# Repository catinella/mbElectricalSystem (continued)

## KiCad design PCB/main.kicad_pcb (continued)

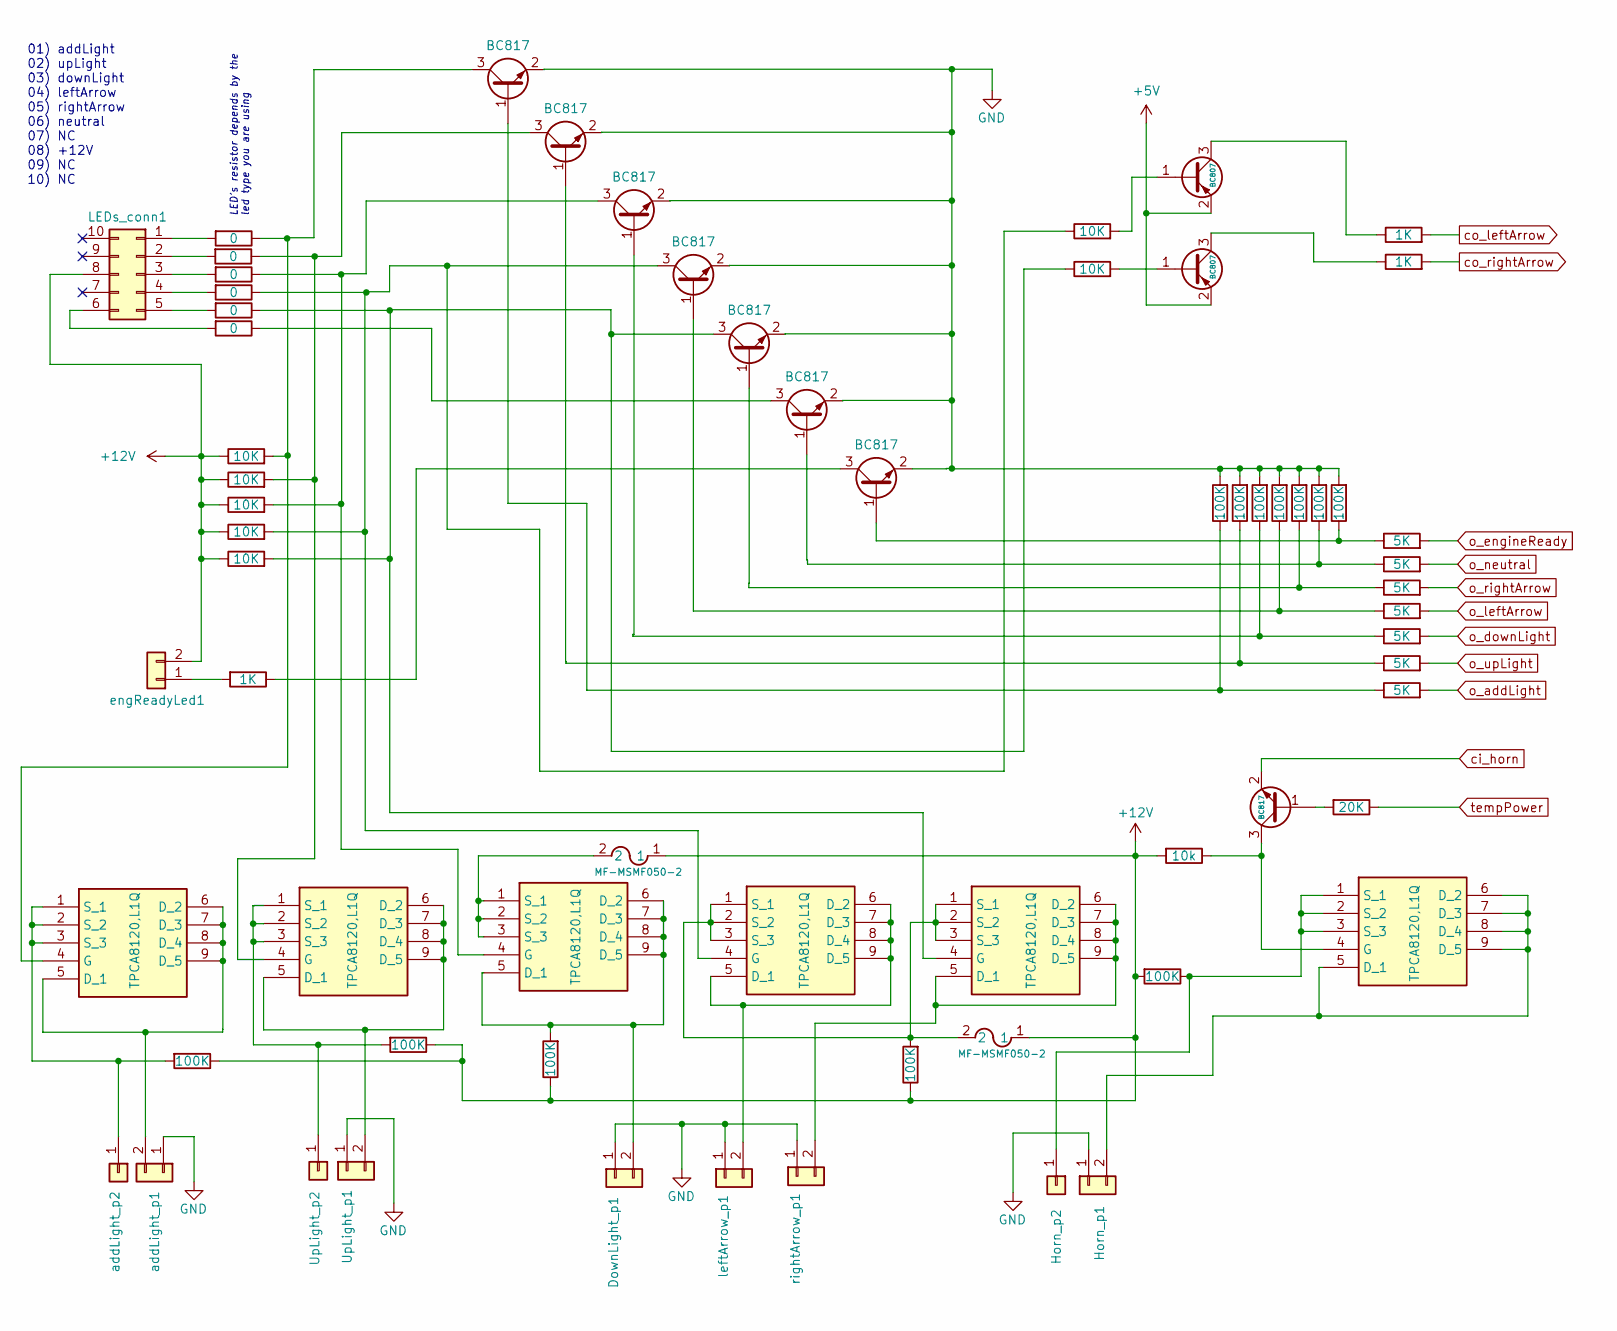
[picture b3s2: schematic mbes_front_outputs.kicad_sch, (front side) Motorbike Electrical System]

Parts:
DownLight_p1: Conn_01x02; PinHeader_1x02_P2.54mm_Vertical
F1, F2: MF-MSMF050-2; FUSE_F050-2
Horn_p1: Conn_01x02; JST_VH_B2P-VH-FB-B_1x02_P3.96mm_Vertical
Horn_p2: Conn_01x01; SolderWire-1sqmm_1x01_D1.4mm_OD2.7mm
LEDs_conn1: Conn_02x05_Counter_Clockwise; PinHeader_2x05_P2.54mm_Vertical
Q1, Q20: BC807; SOT-23
Q5, Q6, Q7, Q12, Q16, Q18: TPCA8120,L1Q; TPH4R003NLL1Q; Mouser Part Number 757-TPCA8120L1Q
Q8, Q9, Q10, Q11, Q13, Q14, Q15, Q17: BC817; SOT-23
RA3, RA4, RA5, RA6, RA7, RA8: 0; R_1206_3216Metric
RA9, RA10, RA11, RA12, RA13, RA37, RA38: 10K; R_1206_3216Metric
RA14, RA43, RA44: 1K; R_1206_3216Metric
RA15, RA16, RA17, RA18, RA19, RA20, RA22, RA23, RA24, RA25, RA27, RA28: 100K; R_1206_3216Metric
RA21: 10k; R_1206_3216Metric
RA29: 20K; R_1206_3216Metric
RA30, RA31, RA32, RA33, RA34, RA35, RA36: 5K; R_1206_3216Metric
UpLight_p1: Conn_01x02; JST_VH_B2P-VH-FB-B_1x02_P3.96mm_Vertical
UpLight_p2: Conn_01x01; SolderWire-1sqmm_1x01_D1.4mm_OD2.7mm
addLight_p1: Conn_01x02; JST_VH_B2P-VH-FB-B_1x02_P3.96mm_Vertical
addLight_p2: Conn_01x01; SolderWire-1sqmm_1x01_D1.4mm_OD2.7mm
engReadyLed1: Conn_01x02; PinHeader_1x02_P2.54mm_Vertical
leftArrow_p1: Conn_01x02; PinHeader_1x02_P2.54mm_Vertical
rightArrow_p1: Conn_01x02; PinHeader_1x02_P2.54mm_Vertical

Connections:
5V: Q1.2 (E), Q20.2 (E); also elsewhere on the board
+12V: F1.1, F2.1, LEDs_conn1.8, RA9.1, RA10.1, RA11.1, RA12.1, RA13.1, RA15.1, RA16.1, RA17.1, RA18.1, RA19.2, RA21.2, engReadyLed1.2; also elsewhere on the board
GND: DownLight_p1.1, Horn_p1.1, Q8.2 (E), Q9.2 (E), Q10.2 (E), Q11.2 (E), Q13.2 (E), Q14.2 (E), Q15.2 (E), RA20.2, RA22.2, RA23.2, RA24.2, RA25.2, RA27.2, RA28.2, UpLight_p1.1, addLight_p1.1, leftArrow_p1.1, rightArrow_p1.1; also elsewhere on the board
unnamed: DownLight_p1.2, Q7.5 (D_1), Q7.6 (D_2), Q7.7 (D_3), Q7.8 (D_4), Q7.9 (D_5), RA17.2
unnamed: Horn_p1.2, Q18.5 (D_1), Q18.6 (D_2), Q18.7 (D_3), Q18.8 (D_4), Q18.9 (D_5)
unnamed: Horn_p2.1, Q18.1 (S_1), Q18.2 (S_2), Q18.3 (S_3), RA19.1
unnamed: LEDs_conn1.1, RA4.2
unnamed: LEDs_conn1.2, RA3.2
unnamed: LEDs_conn1.3, RA5.2
unnamed: LEDs_conn1.4, RA6.2
unnamed: LEDs_conn1.5, RA7.2
unnamed: LEDs_conn1.6, RA8.2
unnamed: Q1.1 (B), RA37.2
unnamed: Q1.3 (C), RA43.1
unnamed: Q5.5 (D_1), Q5.6 (D_2), Q5.7 (D_3), Q5.8 (D_4), Q5.9 (D_5), addLight_p1.2
unnamed: Q5.4 (G), Q8.3 (C), RA4.1, RA9.2
unnamed: Q5.1 (S_1), Q5.2 (S_2), Q5.3 (S_3), RA15.2, addLight_p2.1
unnamed: Q6.5 (D_1), Q6.6 (D_2), Q6.7 (D_3), Q6.8 (D_4), Q6.9 (D_5), UpLight_p1.2
unnamed: Q6.4 (G), Q9.3 (C), RA3.1, RA10.2
unnamed: Q6.1 (S_1), Q6.2 (S_2), Q6.3 (S_3), RA16.2, UpLight_p2.1
unnamed: F2.2, Q7.1 (S_1), Q7.2 (S_2), Q7.3 (S_3)
unnamed: Q8.1 (B), RA20.1, RA36.1
unnamed: Q9.1 (B), RA22.1, RA35.1
unnamed: Q10.1 (B), RA23.1, RA34.1
unnamed: Q7.4 (G), Q10.3 (C), RA5.1, RA11.2
unnamed: Q11.1 (B), RA24.1, RA33.1
unnamed: Q11.3 (C), Q12.4 (G), RA6.1, RA12.2, RA37.1
unnamed: Q12.5 (D_1), Q12.6 (D_2), Q12.7 (D_3), Q12.8 (D_4), Q12.9 (D_5), leftArrow_p1.2
unnamed: F1.2, Q12.1 (S_1), Q12.2 (S_2), Q12.3 (S_3), Q16.1 (S_1), Q16.2 (S_2), Q16.3 (S_3), RA18.2
unnamed: Q13.1 (B), RA25.1, RA32.1
unnamed: Q13.3 (C), Q16.4 (G), RA7.1, RA13.2, RA38.1
unnamed: Q14.1 (B), RA27.1, RA31.1
unnamed: Q14.3 (C), RA8.1
unnamed: Q15.1 (B), RA28.1, RA30.1
unnamed: Q15.3 (C), RA14.1
unnamed: Q16.5 (D_1), Q16.6 (D_2), Q16.7 (D_3), Q16.8 (D_4), Q16.9 (D_5), rightArrow_p1.2
unnamed: Q17.1 (B), RA29.2
unnamed: Q17.3 (C), Q18.4 (G), RA21.1
unnamed: Q20.1 (B), RA38.2
unnamed: Q20.3 (C), RA44.1
unnamed: RA14.2, engReadyLed1.1
ci_horn: Q17.2 (E); also elsewhere on the board
co_leftArrow: RA43.2; also elsewhere on the board
co_rightArrow: RA44.2; also elsewhere on the board
o_addLight: RA36.2; also elsewhere on the board
o_downLight: RA34.2; also elsewhere on the board
o_engineReady: RA30.2; also elsewhere on the board
o_leftArrow: RA33.2; also elsewhere on the board
o_neutral: RA31.2; also elsewhere on the board
o_rightArrow: RA32.2; also elsewhere on the board
o_upLight: RA35.2; also elsewhere on the board
tempPower: RA29.1; also elsewhere on the board

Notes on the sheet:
LED's resistor depends by the led type you are using
01) addLight 02) upLight 03) downLight 04) leftArrow 05) rightArrow 06) neutral 07) NC 08) +12V 09) NC 10) NC

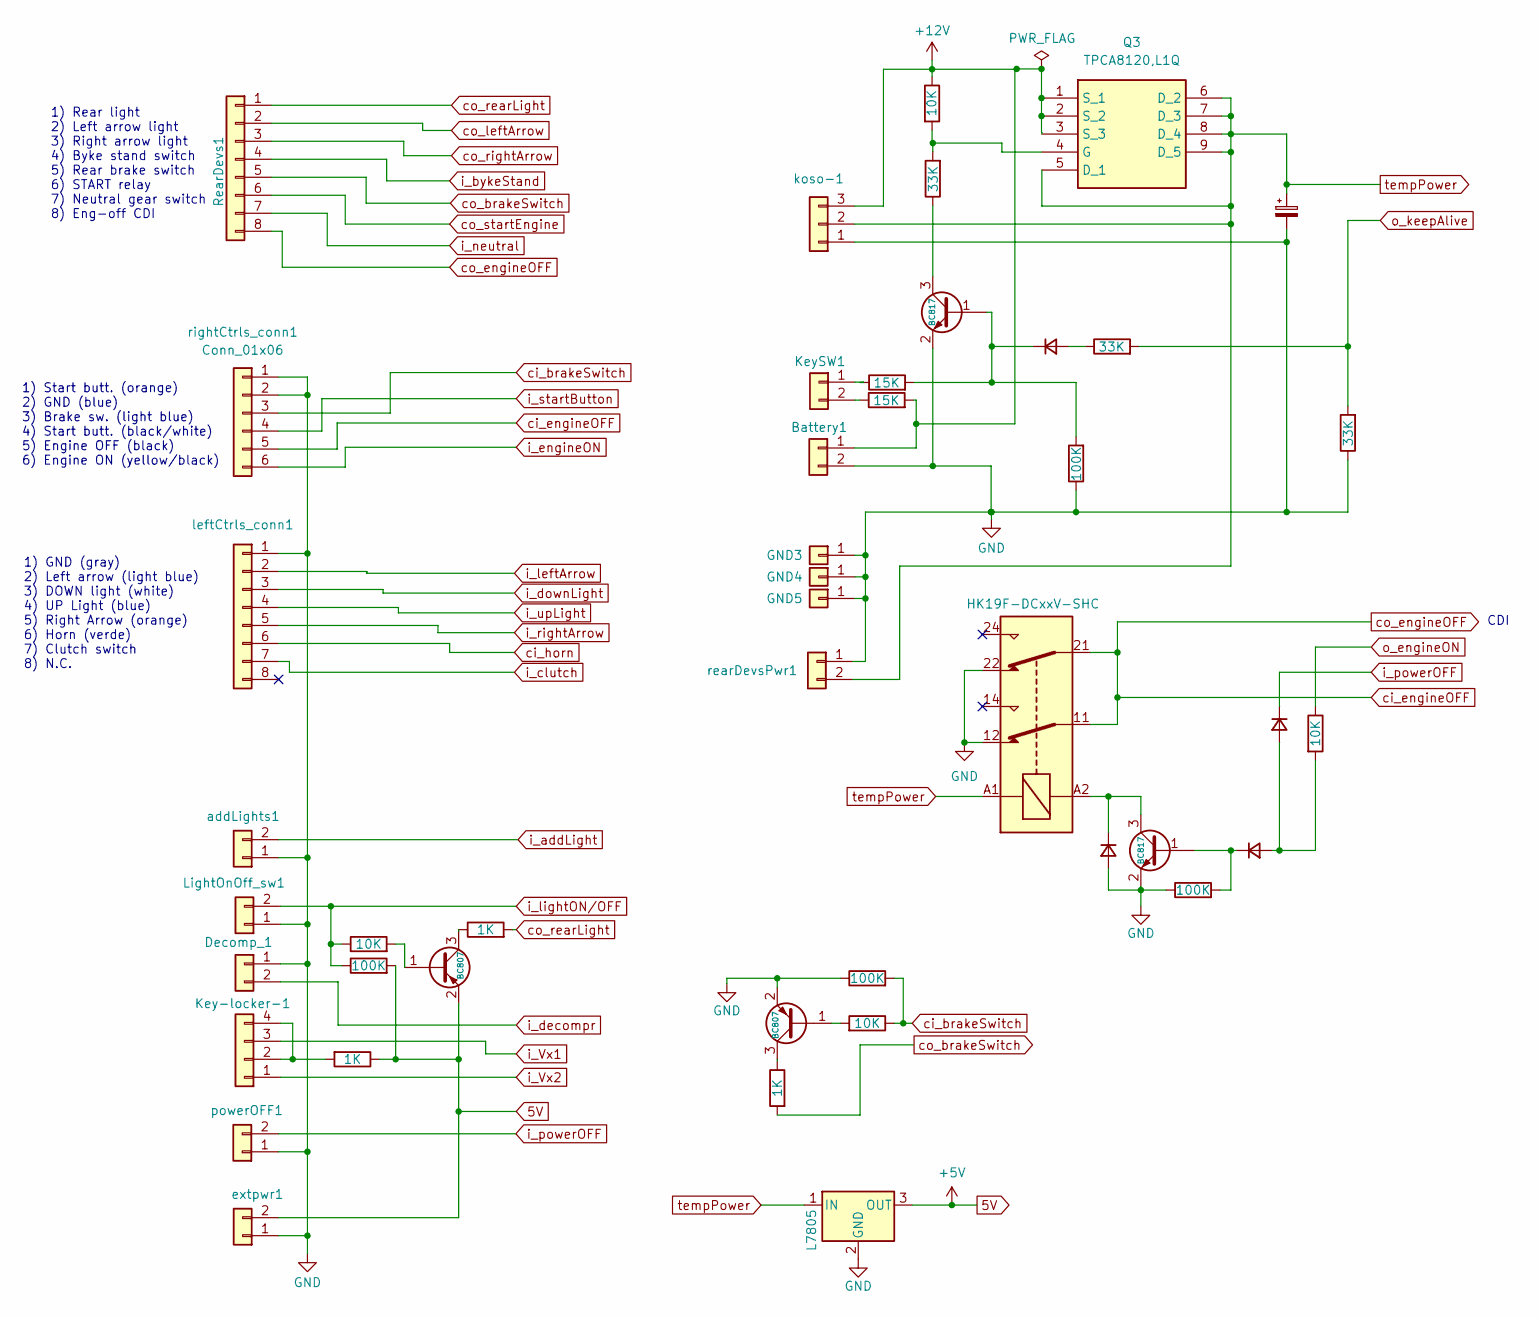
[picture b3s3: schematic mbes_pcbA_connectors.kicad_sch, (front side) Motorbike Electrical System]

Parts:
Battery1: Conn_01x02; JST_VH_B2P-VH-FB-B_1x02_P3.96mm_Vertical
C2: C_Polarized_Small; CP_Radial_D8.0mm_P2.50mm
D1, D2, D3: PMEG40T30ER; Nexperia_CFP3_SOD-123W
Decomp_1: Conn_01x02; PinHeader_1x02_P2.54mm_Vertical
GND3, GND4, GND5: Conn_01x01; SolderWire-1sqmm_1x01_D1.4mm_OD2.7mm
K1: HK19F-DCxxV-SHC; Relay_DPDT_Finder_30.22
Key-locker-1: Conn_01x04; PinHeader_1x04_P2.54mm_Vertical
KeySW1: Conn_01x02; PinHeader_1x02_P2.54mm_Vertical
LightOnOff_sw1: Conn_01x02; PinHeader_1x02_P2.54mm_Vertical
Q2, Q4: BC817; SOT-23
Q3: TPCA8120,L1Q; TPH4R003NLL1Q; Manufacturer_Part_Number TPCA8120,L1Q; Mouser Part Number 757-TPCA8120L1Q
Q22, Q24: BC807; SOT-23
R6: 1K; R_1206_3216Metric
R7, R8: 15K; R_1206_3216Metric
R9: 10K; R_1206_3216Metric
R10, R11, R12: 33K; R_1206_3216Metric
R13: 100K; R_1206_3216Metric
RA1, RA41, RA47: 100K; R_1206_3216Metric
RA2, RA40, RA46: 10K; R_1206_3216Metric
RA42, RA48: 1K; R_1206_3216Metric
RearDevs1: Conn_01x08; PinHeader_1x08_P2.54mm_Vertical
U2: L7805; TO-220-3_Vertical
addLights1: Conn_01x02; PinHeader_1x02_P2.54mm_Vertical
extpwr1: Conn_01x02; PinHeader_1x02_P2.54mm_Vertical
flyback-1: PMEG40T30ER; Nexperia_CFP3_SOD-123W
koso-1: Conn_01x03; PinHeader_1x03_P2.54mm_Vertical
leftCtrls_conn1: Conn_01x08; PinHeader_1x08_P2.54mm_Vertical
powerOFF1: Conn_01x02; PinHeader_1x02_P2.54mm_Vertical
rearDevsPwr1: Conn_01x02; PinHeader_1x02_P2.54mm_Vertical
rightCtrls_conn1: Conn_01x06; PinHeader_1x06_P2.54mm_Vertical

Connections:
5V: Q22.2 (E), R6.1, RA47.2, U2.3 (OUT), extpwr1.2; also elsewhere on the board
+12V: Battery1.1, Q3.1 (S_1), Q3.2 (S_2), Q3.3 (S_3), R7.2, R9.1, koso-1.3; also elsewhere on the board
GND: Battery1.2, C2.2, Decomp_1.1, GND3.1, GND4.1, GND5.1, K1.12, K1.22, LightOnOff_sw1.1, Q2.2 (E), Q4.2 (E), Q24.2 (E), R12.1, R13.1, RA1.1, RA41.1, U2.2 (GND), addLights1.1, extpwr1.1, flyback-1.2 (A), koso-1.1, leftCtrls_conn1.1, powerOFF1.1, rearDevsPwr1.1, rightCtrls_conn1.1, rightCtrls_conn1.2; also elsewhere on the board
unnamed: D1.2 (A), R11.1
unnamed: D1.1 (K), Q2.1 (B), R8.2, R13.2
unnamed: D2.2 (A), D3.2 (A), RA2.2
unnamed: D2.1 (K), Q4.1 (B), RA1.2
unnamed: Key-locker-1.2, Key-locker-1.4, R6.2
unnamed: KeySW1.1, R8.1
unnamed: KeySW1.2, R7.1
unnamed: Q2.3 (C), R10.1
unnamed: Q3.4 (G), R9.2, R10.2
unnamed: K1.A2, Q4.3 (C), flyback-1.1 (K)
unnamed: Q22.1 (B), RA46.2
unnamed: Q22.3 (C), RA48.1
unnamed: Q24.1 (B), RA40.2
unnamed: Q24.3 (C), RA42.1
ci_brakeSwitch: RA40.1, RA41.2, rightCtrls_conn1.3
ci_engineOFF: K1.11, K1.21, RearDevs1.8, rightCtrls_conn1.5
ci_horn: leftCtrls_conn1.6; also elsewhere on the board
co_brakeSwitch: RA42.2, RearDevs1.5
co_leftArrow: RearDevs1.2; also elsewhere on the board
co_rearLight: RA48.2, RearDevs1.1
co_rightArrow: RearDevs1.3; also elsewhere on the board
co_startEngine: RearDevs1.6; also elsewhere on the board
i_Vx1: Key-locker-1.3; also elsewhere on the board
i_Vx2: Key-locker-1.1; also elsewhere on the board
i_addLight: addLights1.2; also elsewhere on the board
i_bykeStand: RearDevs1.4; also elsewhere on the board
i_clutch: leftCtrls_conn1.7; also elsewhere on the board
i_decompr: Decomp_1.2; also elsewhere on the board
i_downLight: leftCtrls_conn1.3; also elsewhere on the board
i_engineON: rightCtrls_conn1.6; also elsewhere on the board
i_leftArrow: leftCtrls_conn1.2; also elsewhere on the board
i_lightON/OFF: LightOnOff_sw1.2, RA46.1, RA47.1; also elsewhere on the board
i_neutral: RearDevs1.7; also elsewhere on the board
i_powerOFF: D3.1 (K), powerOFF1.2; also elsewhere on the board
i_rightArrow: leftCtrls_conn1.5; also elsewhere on the board
i_startButton: rightCtrls_conn1.4; also elsewhere on the board
i_upLight: leftCtrls_conn1.4; also elsewhere on the board
o_engineON: RA2.1; also elsewhere on the board
o_keepAlive: R11.2, R12.2; also elsewhere on the board
tempPower: C2.1, K1.A1, Q3.5 (D_1), Q3.6 (D_2), Q3.7 (D_3), Q3.8 (D_4), Q3.9 (D_5), U2.1 (IN), koso-1.2, rearDevsPwr1.2; also elsewhere on the board

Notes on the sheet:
1) Start butt. (orange) 2) GND (blue) 3) Brake sw. (light blue) 4) Start butt. (black/white) 5) Engine OFF (black) 6) Engine ON (yellow/black)
1) GND (gray) 2) Left arrow (light blue) 3) DOWN light (white) 4) UP Light (blue) 5) Right Arrow (orange) 6) Horn (verde) 7) Clutch switch 8) N.C.
1) Rear light 2) Left arrow light 3) Right arrow light 4) Byke stand switch 5) Rear brake switch 6) START relay 7) Neutral gear switch 8) Eng-off CDI
CDI

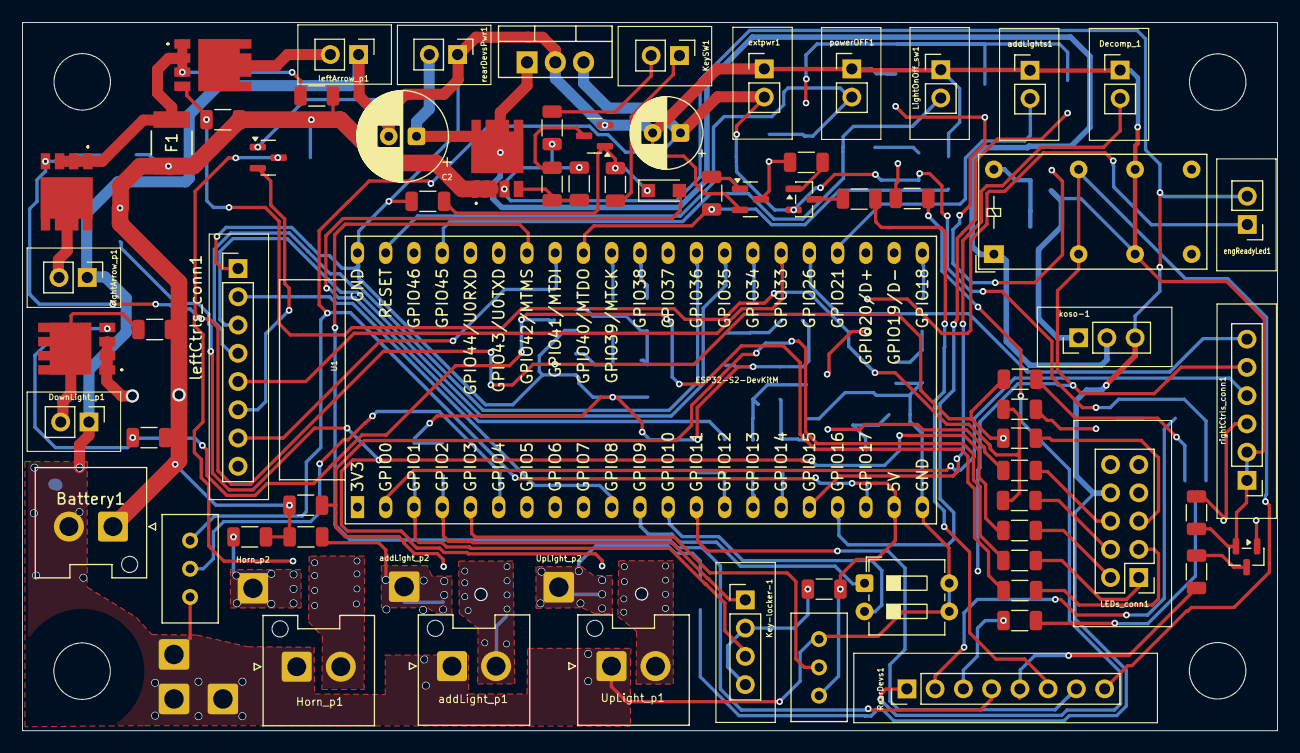
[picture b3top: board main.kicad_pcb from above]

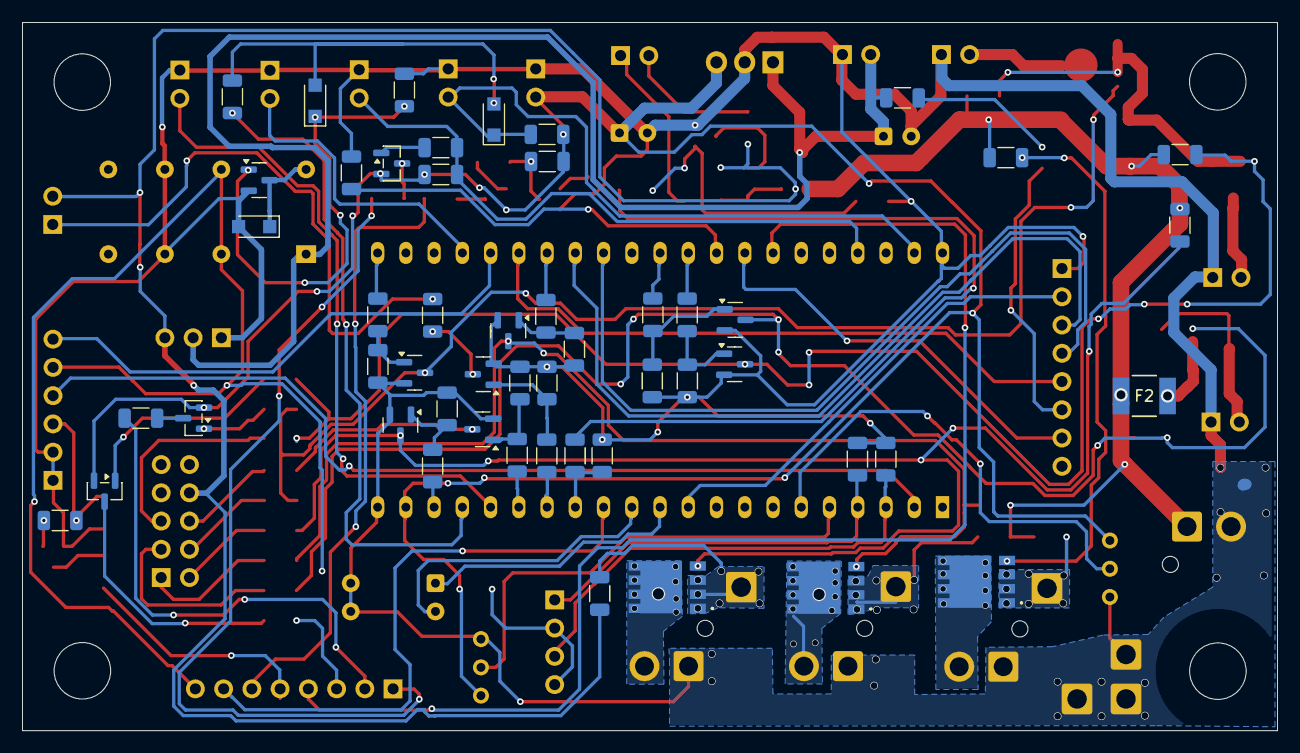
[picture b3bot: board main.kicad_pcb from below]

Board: 2 copper layers, 112.9 x 63.7 mm, 125 parts (51 on the bottom side), 97 nets.

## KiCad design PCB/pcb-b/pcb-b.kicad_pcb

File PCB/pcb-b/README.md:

## 1.0 Files

|       Files/Directories      | Description                          |
|------------------------------|--------------------------------------|
| pcb-b.kicad_sch              | Main electric scheme                 |
| mbes_front_outputs.kicad_sch | Output lines electric scheme         |
| pcb-b.kicad_pcb              | PCB                                  |

(*) This project is covered by the GPL-3. Please read that file for further information.

## 2.0 Description:
This folder contains all files you need to modify/build the PCB that implements the power stage for the motorbike front-side
connected devices (e.g. low-beam light, high-beam light, direction indicators, horn...). This PCB also provides the following features:

- It locks the engine when the vehicle is turned off, using CDI
- It provides temporary electric current to the controller's MCU for key authentication
- It provides electric current when the key has been authenticated

### 2.1 Power stage
In order to provide electric current to the motorbike's devices (lights, horn...), I have used the
[TPCA8120](https://static.chipdip.ru/lib/624/DOC060624975.pdf) P-Channel MOS. Its low drain-source on-resistance (4mOhm) allows this 
electronic circuit to avoid wasting electric power with high current too. For example, with a 60W (5A) light, it wastes just 20mW!!
It can also support 10A current and it is very small. But, at the moment, the whole  PCB is planed for lower current. The following table
shows the common devices and their max and expected needed current. The expected values have been measured on my Suzuki DR350
with LED lights.

| Device           | Expected current | Max current |
|------------------|------------------|-------------|
| low-beam light   | 200mA  (2.4W)    | 500mA (6W)  |
| high beam-light  | 2A     (24W)     | 6A    (72W) |
| dir-indicator    | <100mA (1.2W)    | 500mA (6W)  |
| horn             | 2A     (24W)     | 6A    (72W) |
| additinal light  | 2A     (24W)     | 6A    (72W) |

### 2.2 Fuses
To reduce the number of external fuses, all devices that require less than 6W use 
[MSMF050](https://www.bourns.com/docs/product-datasheets/mf-msmf.pdf) PTC resettable fuses.
As you can see in the component's datasheet, it can handle up to 500mA current and stop currents over 1A.
With this solution, only 3 external (5A) fuses are needed, plus the (20A) general one.

### 2.3 Engine locking mechanism
As in all motorbikes, in order to avoid that the engine can be started when the motorbike is locked, the proper CDI pin must be
connected to GND. To achieve this result and to protect the circuit from unknown electric voltage from the CDI, I have 
used the relay [HK19-DC12V](https://grobotronics.com/images/datasheets/HK19F-12V.pdf) instead of a modern N-Channel MOS.

In order to manage the concurrency events of the power-off button and the engine electronic management, I have used the
[PMEG40T30ER](https://assets.nexperia.com/documents/data-sheet/PMEG40T30ER.pdf) low Trench MEGA Schottky barrier rectifier.

### 2.4 Cables and internal connectors
In order to connect this power stage with the master controller PCB, two
[10-pin dual-row connectors](https://www.molex.com/en-us/products/part-detail/702461004?display=pdf) have been used. For
further details, read the PCB-a documentation.

For the cables to the electric consumers (e.g. lights, horn...), you can use **AWG18 cable**. It is thin enough but can handle
**6A** electric current without problems. You can use the same cable also for the electric wire connected to the fuses.

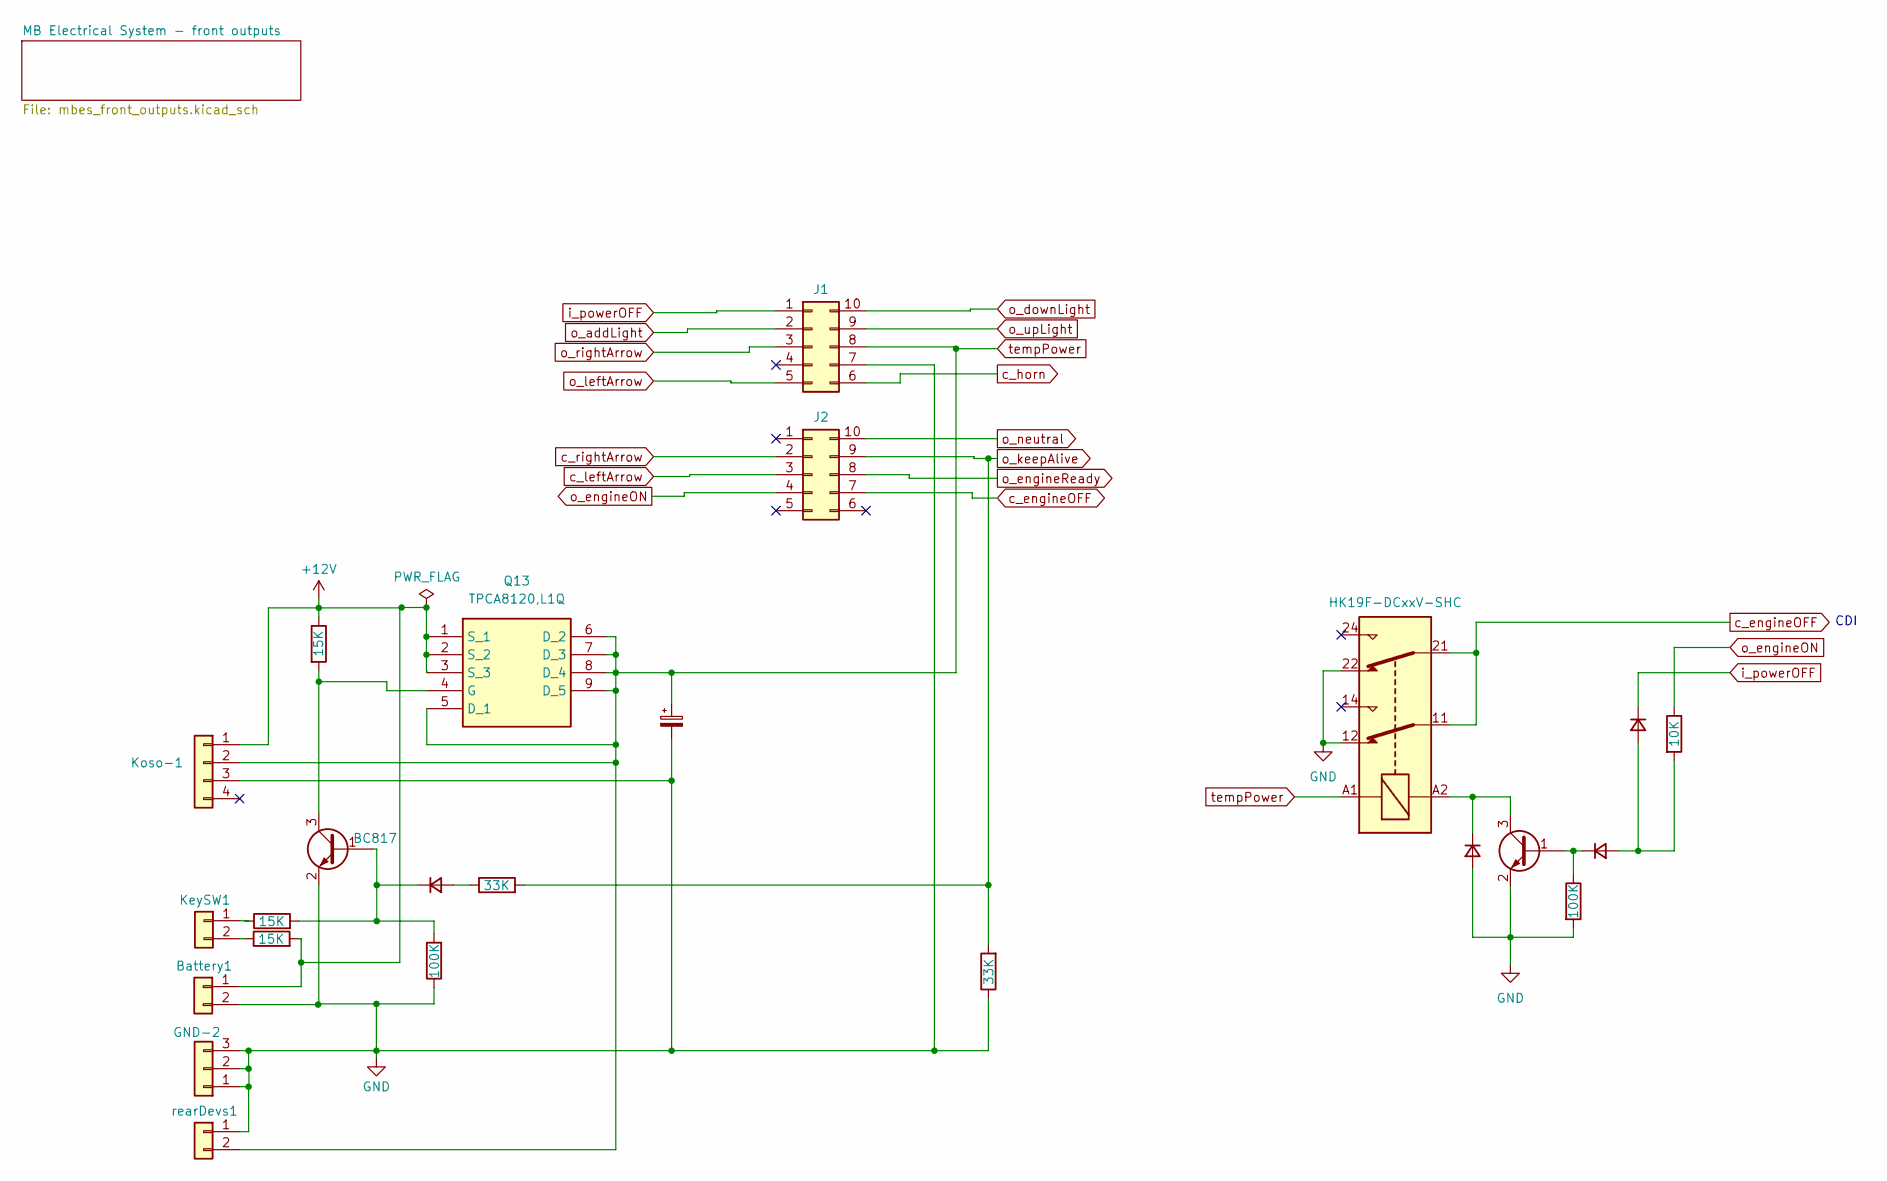
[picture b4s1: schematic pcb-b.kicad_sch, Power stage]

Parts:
Battery1: Conn_01x02; SolderWire-1sqmm_1x02_P5.4mm_D1.4mm_OD2.7mm
C9: C_Polarized_Small; CP_Radial_D8.0mm_P2.50mm
D1, D2, D3: PMEG40T30ER; Nexperia_CFP3_SOD-123W
GND-2: SolderWire-0.75sqmm_1x03_P4.8mm_D1.25mm_OD2.3mm
J1, J2: Conn_02x05_Counter_Clockwise; PinHeader_2x05_P2.54mm_Vertical
K1: HK19F-DCxxV-SHC; Relay_DPDT_Finder_30.22
KeySW1: Conn_01x02; PinHeader_1x02_P2.54mm_Vertical
Koso-1: Conn_01x04; PinHeader_1x04_P2.54mm_Vertical
Q3, Q9: BC817; SOT-23
Q13: TPCA8120,L1Q; TPH4R003NLL1Q; Manufacturer_Part_Number TPCA8120,L1Q; Mouser Part Number 757-TPCA8120L1Q
R1, R2, R4: 15K; R_1206_3216Metric
R5, R6: 33K; R_1206_3216Metric
R7: 100K; R_1206_3216Metric
RA8: 100K; R_1206_3216Metric
RA15: 10K; R_1206_3216Metric
flyback-1: PMEG40T30ER; Nexperia_CFP3_SOD-123W
rearDevs1: Conn_01x02; PinHeader_1x02_P2.54mm_Vertical

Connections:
+12V: Battery1.1, Koso-1.1, Q13.1 (S_1), Q13.2 (S_2), Q13.3 (S_3), R1.2, R2.1; also elsewhere on the board
GND: Battery1.2, C9.2, GND-2.1, GND-2.2, GND-2.3, J1.7, K1.12, K1.22, Koso-1.3, Q3.2 (E), Q9.2 (E), R6.1, R7.1, RA8.2, flyback-1.2 (A), rearDevs1.1; also elsewhere on the board
unnamed: D1.2 (A), R5.1
unnamed: D1.1 (K), Q9.1 (B), R4.2, R7.2
unnamed: D2.2 (A), D3.2 (A), RA15.2
unnamed: D2.1 (K), Q3.1 (B), RA8.1
unnamed: KeySW1.1, R4.1
unnamed: KeySW1.2, R1.1
unnamed: K1.A2, Q3.3 (C), flyback-1.1 (K)
unnamed: Q9.3 (C), Q13.4 (G), R2.2
c_engineOFF: J2.7, K1.11, K1.21
c_horn: J1.6; also elsewhere on the board
c_leftArrow: J2.3; also elsewhere on the board
c_rightArrow: J2.2; also elsewhere on the board
i_powerOFF: D3.1 (K), J1.1
o_addLight: J1.2; also elsewhere on the board
o_downLight: J1.10; also elsewhere on the board
o_engineON: J2.4, RA15.1
o_engineReady: J2.8; also elsewhere on the board
o_keepAlive: J2.9, R5.2, R6.2
o_leftArrow: J1.5; also elsewhere on the board
o_neutral: J2.10; also elsewhere on the board
o_rightArrow: J1.3; also elsewhere on the board
o_upLight: J1.9; also elsewhere on the board
tempPower: C9.1, J1.8, K1.A1, Koso-1.2, Q13.5 (D_1), Q13.6 (D_2), Q13.7 (D_3), Q13.8 (D_4), Q13.9 (D_5), rearDevs1.2; also elsewhere on the board

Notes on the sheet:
CDI

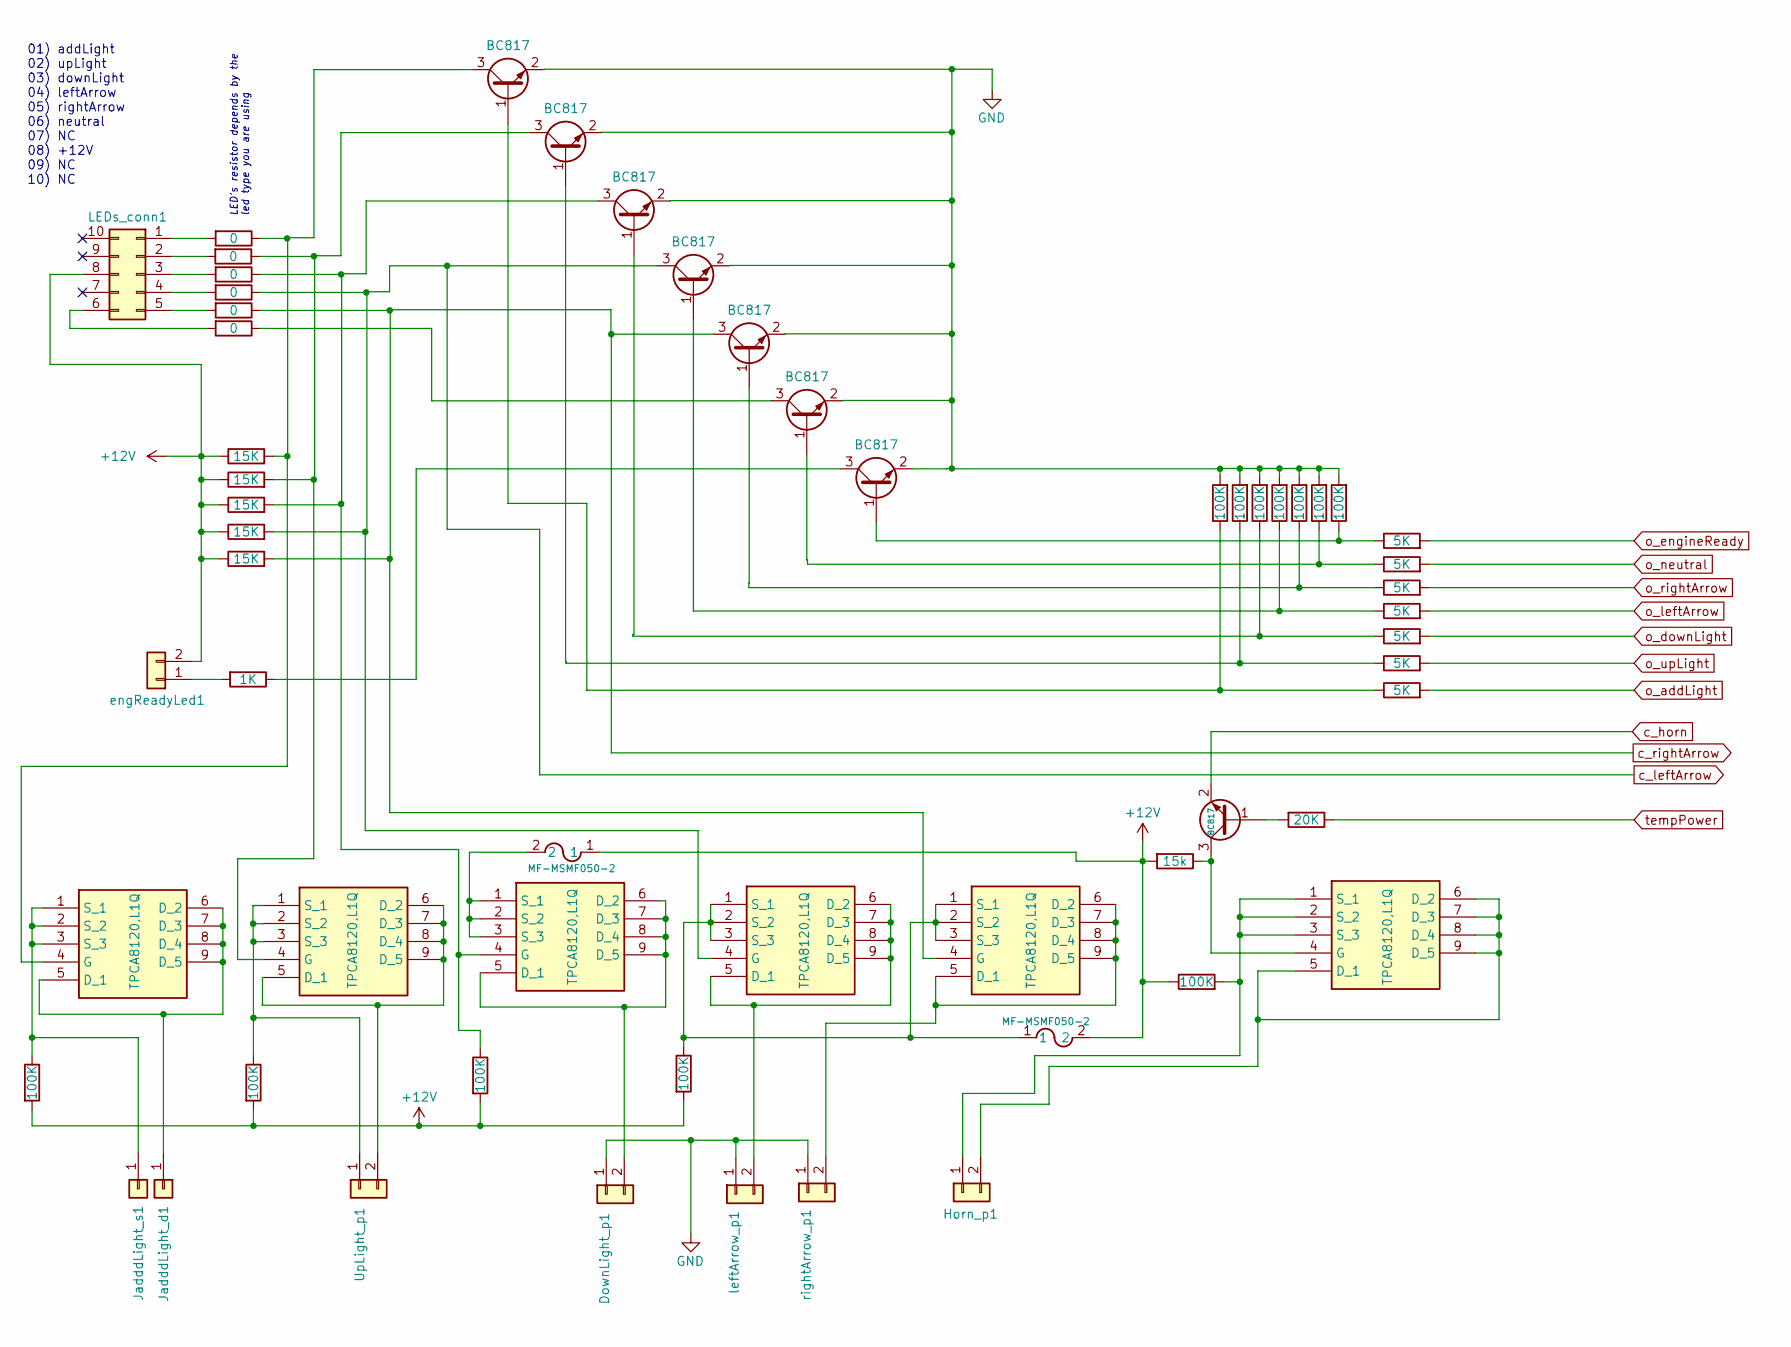
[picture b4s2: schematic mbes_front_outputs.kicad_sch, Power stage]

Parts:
DownLight_p1: Conn_01x02; PinHeader_1x02_P2.54mm_Vertical
F1, F2: MF-MSMF050-2; FUSE_F050-2
Horn_p1: Conn_01x02; SolderWire-1sqmm_1x02_P5.4mm_D1.4mm_OD2.7mm
JadddLight_d1: Conn_01x01; SolderWire-1sqmm_1x01_D1.4mm_OD2.7mm
JadddLight_s1: Conn_01x01; SolderWire-1sqmm_1x01_D1.4mm_OD2.7mm
LEDs_conn1: Conn_02x05_Counter_Clockwise; PinHeader_2x05_P2.54mm_Vertical
Q1, Q2, Q10, Q14, Q15, Q19, Q20, Q21: BC817; SOT-23
Q4, Q5, Q6, Q7, Q8, Q11: TPCA8120,L1Q; TPH4R003NLL1Q; Mouser Part Number 757-TPCA8120L1Q
RA1, RA2, RA3, RA4, RA5, RA6: 0; R_1206_3216Metric
RA7, RA10, RA11, RA12, RA13, RA34, RA35, RA36, RA37, RA38, RA39, RA40: 100K; R_1206_3216Metric
RA9: 1K; R_1206_3216Metric
RA16, RA17, RA18, RA19, RA20, RA21, RA22: 5K; R_1206_3216Metric
RA23: 20K; R_1206_3216Metric
RA24, RA25, RA26, RA27, RA28: 15K; R_1206_3216Metric
RA42: 15k; R_1206_3216Metric
UpLight_p1: Conn_01x02; SolderWire-1sqmm_1x02_P5.4mm_D1.4mm_OD2.7mm
engReadyLed1: Conn_01x02; PinHeader_1x02_P2.54mm_Vertical
leftArrow_p1: Conn_01x02; PinHeader_1x02_P2.54mm_Vertical
rightArrow_p1: Conn_01x02; PinHeader_1x02_P2.54mm_Vertical

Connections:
+12V: F1.1, F2.2, LEDs_conn1.8, RA7.2, RA10.2, RA11.2, RA12.2, RA13.1, RA24.1, RA25.1, RA26.1, RA27.1, RA28.1, RA42.2, engReadyLed1.2; also elsewhere on the board
GND: DownLight_p1.1, Q1.2 (E), Q2.2 (E), Q14.2 (E), Q15.2 (E), Q19.2 (E), Q20.2 (E), Q21.2 (E), RA34.2, RA35.2, RA36.2, RA37.2, RA38.2, RA39.2, RA40.2, leftArrow_p1.1, rightArrow_p1.1; also elsewhere on the board
unnamed: DownLight_p1.2, Q5.5 (D_1), Q5.6 (D_2), Q5.7 (D_3), Q5.8 (D_4), Q5.9 (D_5)
unnamed: Horn_p1.1, Q8.1 (S_1), Q8.2 (S_2), Q8.3 (S_3), RA13.2
unnamed: Horn_p1.2, Q8.5 (D_1), Q8.6 (D_2), Q8.7 (D_3), Q8.8 (D_4), Q8.9 (D_5)
unnamed: JadddLight_d1.1, Q11.5 (D_1), Q11.6 (D_2), Q11.7 (D_3), Q11.8 (D_4), Q11.9 (D_5)
unnamed: JadddLight_s1.1, Q11.1 (S_1), Q11.2 (S_2), Q11.3 (S_3), RA7.1
unnamed: LEDs_conn1.1, RA1.2
unnamed: LEDs_conn1.2, RA2.2
unnamed: LEDs_conn1.3, RA3.2
unnamed: LEDs_conn1.4, RA4.2
unnamed: LEDs_conn1.5, RA5.2
unnamed: LEDs_conn1.6, RA6.2
unnamed: Q1.1 (B), RA22.1, RA34.1
unnamed: Q1.3 (C), Q11.4 (G), RA1.1, RA24.2
unnamed: Q2.1 (B), RA21.1, RA35.1
unnamed: Q2.3 (C), Q4.4 (G), RA2.1, RA25.2
unnamed: Q4.5 (D_1), Q4.6 (D_2), Q4.7 (D_3), Q4.8 (D_4), Q4.9 (D_5), UpLight_p1.2
unnamed: Q4.1 (S_1), Q4.2 (S_2), Q4.3 (S_3), RA10.1, UpLight_p1.1
unnamed: Q6.5 (D_1), Q6.6 (D_2), Q6.7 (D_3), Q6.8 (D_4), Q6.9 (D_5), leftArrow_p1.2
unnamed: F2.1, Q6.1 (S_1), Q6.2 (S_2), Q6.3 (S_3), Q7.1 (S_1), Q7.2 (S_2), Q7.3 (S_3), RA12.1
unnamed: Q7.5 (D_1), Q7.6 (D_2), Q7.7 (D_3), Q7.8 (D_4), Q7.9 (D_5), rightArrow_p1.2
unnamed: Q10.1 (B), RA23.2
unnamed: Q8.4 (G), Q10.3 (C), RA42.1
unnamed: Q14.1 (B), RA20.1, RA36.1
unnamed: Q15.1 (B), RA19.1, RA37.1
unnamed: Q19.1 (B), RA18.1, RA38.1
unnamed: Q20.1 (B), RA17.1, RA39.1
unnamed: Q20.3 (C), RA6.1
unnamed: Q21.1 (B), RA16.1, RA40.1
unnamed: Q21.3 (C), RA9.1
unnamed: RA9.2, engReadyLed1.1
c_horn: Q10.2 (E); also elsewhere on the board
c_leftArrow: Q6.4 (G), Q15.3 (C), RA4.1, RA27.2; also elsewhere on the board
c_rightArrow: Q7.4 (G), Q19.3 (C), RA5.1, RA28.2; also elsewhere on the board
o_addLight: RA22.2; also elsewhere on the board
o_downLight: RA20.2; also elsewhere on the board
o_engineReady: RA16.2; also elsewhere on the board
o_leftArrow: RA19.2; also elsewhere on the board
o_neutral: RA17.2; also elsewhere on the board
o_rightArrow: RA18.2; also elsewhere on the board
o_upLight: RA21.2; also elsewhere on the board
tempPower: RA23.1; also elsewhere on the board

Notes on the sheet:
LED's resistor depends by the led type you are using
01) addLight 02) upLight 03) downLight 04) leftArrow 05) rightArrow 06) neutral 07) NC 08) +12V 09) NC 10) NC

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
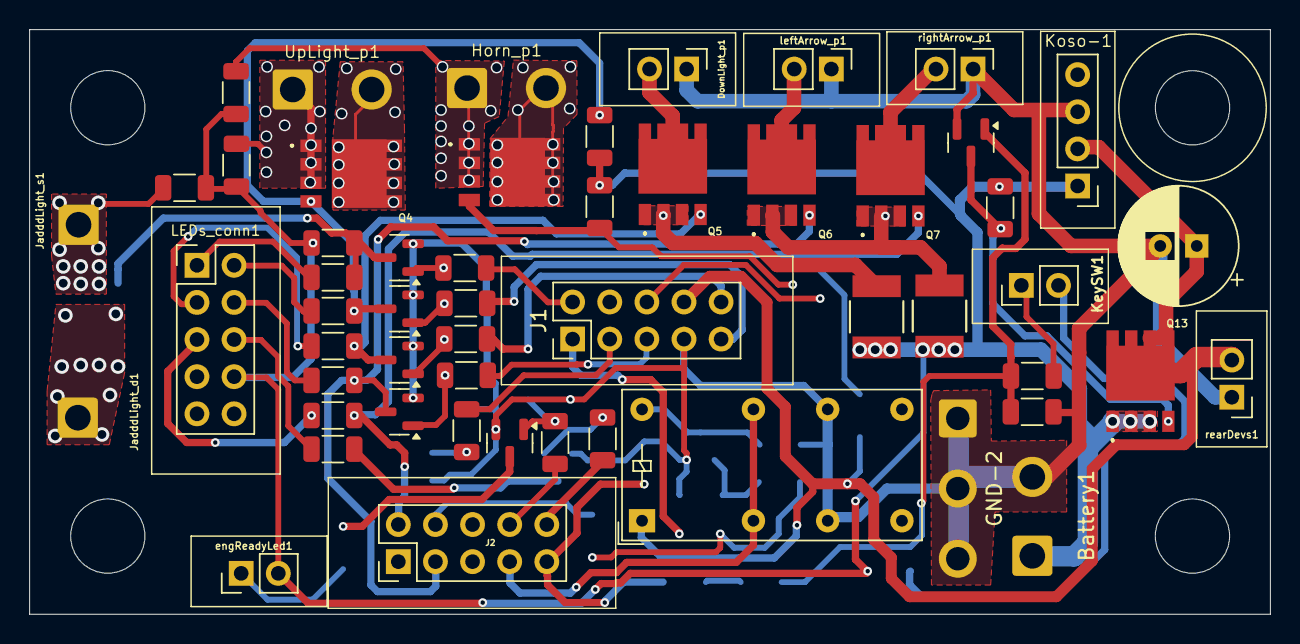
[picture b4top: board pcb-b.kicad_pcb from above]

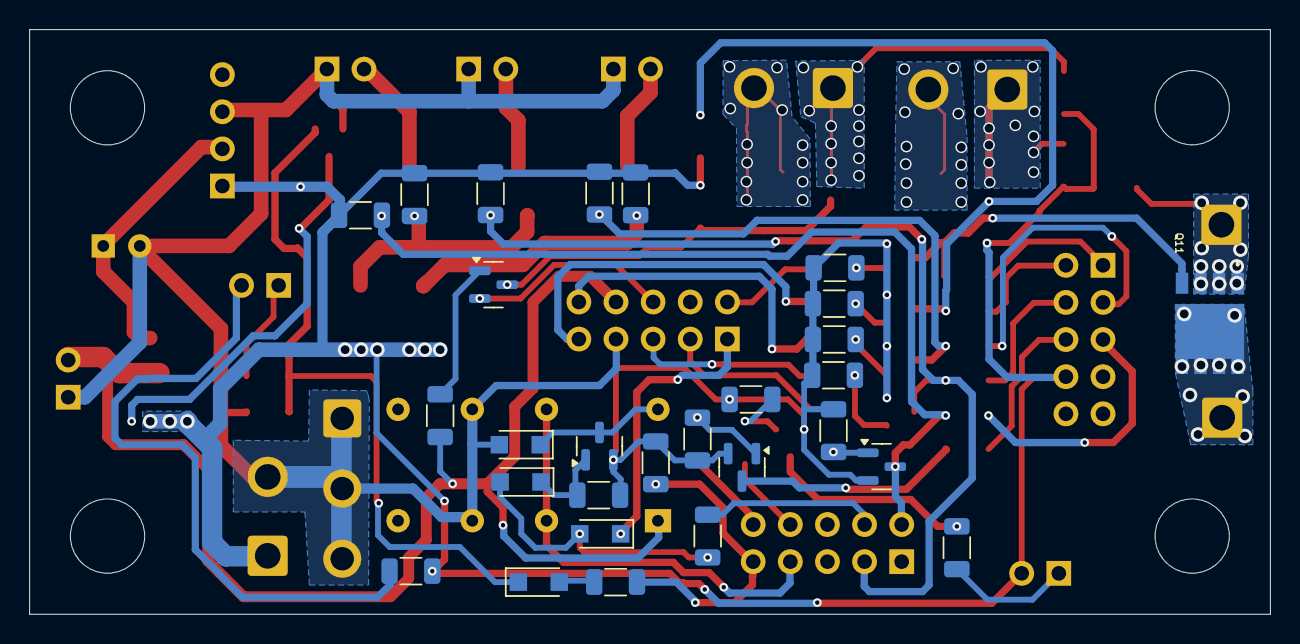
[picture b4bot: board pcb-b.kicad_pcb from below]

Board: 2 copper layers, 84.9 x 40.0 mm, 82 parts (28 on the bottom side), 57 nets.
